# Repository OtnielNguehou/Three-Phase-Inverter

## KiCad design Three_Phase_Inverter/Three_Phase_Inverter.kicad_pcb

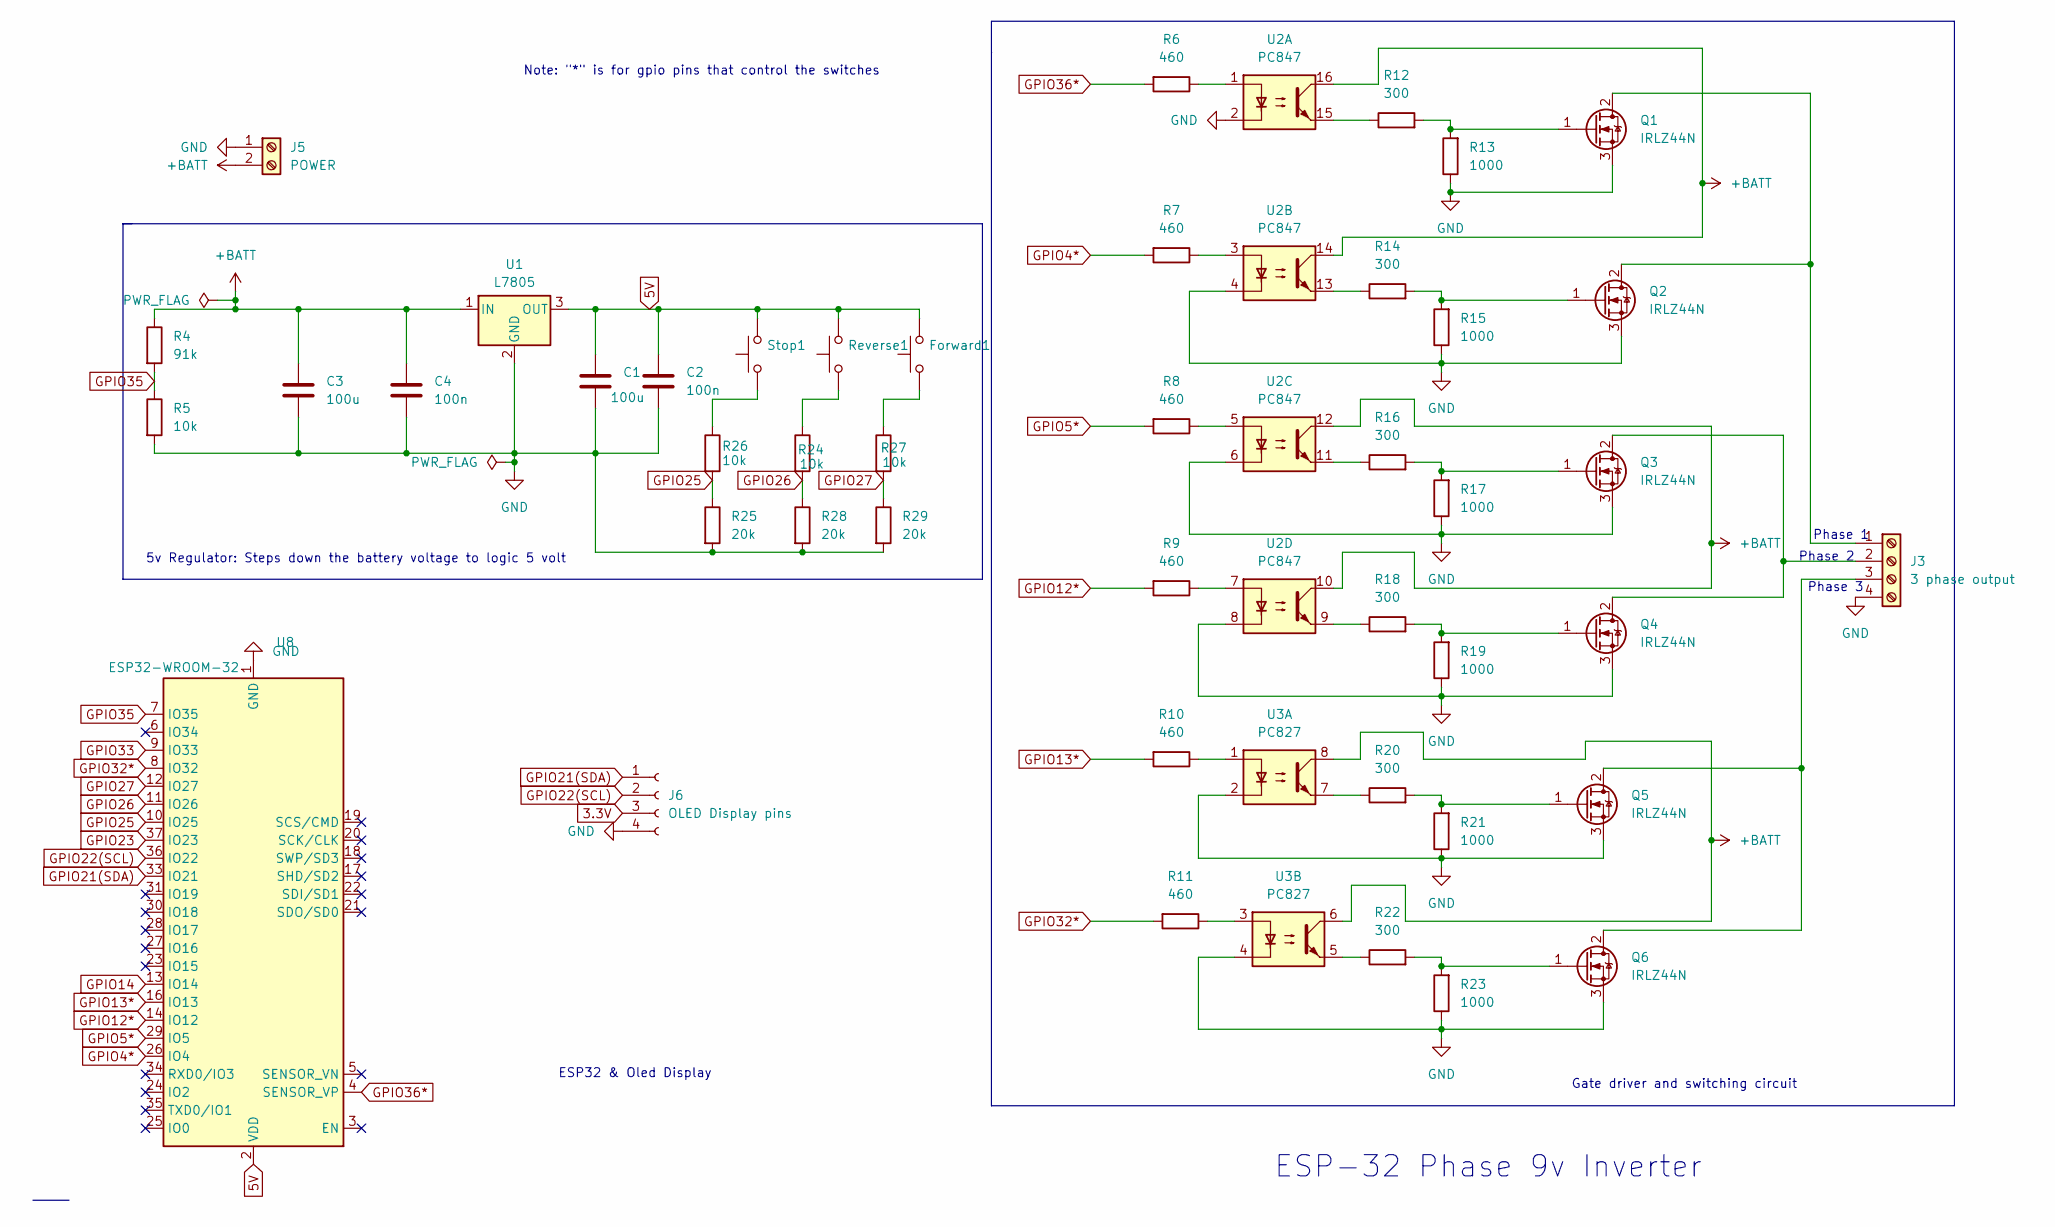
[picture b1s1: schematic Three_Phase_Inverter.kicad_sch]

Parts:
C1, C3: 100u; C_Radial_D5.0mm_H7.0mm_P2.00mm
C2, C4: 100n; C_Radial_D5.0mm_H7.0mm_P2.00mm
Forward1: SW_PUSH_6mm_H7.3mm
J3: 3 phase output; TerminalBlock_Xinya_XY308-2.54-4P_1x04_P2.54mm_Horizontal
J5: POWER; TerminalBlock_MaiXu_MX126-5.0-02P_1x02_P5.00mm
J6: OLED Display pins; PinHeader_1x04_P1.27mm_Vertical
Q1, Q2, Q3, Q4, Q5, Q6: IRLZ44N; TO-220-3_Vertical
R4: 91k; R_Axial_DIN0207_L6.3mm_D2.5mm_P10.16mm_Horizontal
R5, R24, R26, R27: 10k; R_Axial_DIN0207_L6.3mm_D2.5mm_P10.16mm_Horizontal
R6, R7, R8, R9, R10, R11: 460; R_Axial_DIN0207_L6.3mm_D2.5mm_P10.16mm_Horizontal
R12, R14, R16, R18, R20, R22: 300; R_Axial_DIN0207_L6.3mm_D2.5mm_P10.16mm_Horizontal
R13, R15, R17, R19, R21, R23: 1000; R_Axial_DIN0207_L6.3mm_D2.5mm_P10.16mm_Horizontal
R25, R28, R29: 20k; R_Axial_DIN0207_L6.3mm_D2.5mm_P10.16mm_Horizontal
Reverse1: SW_PUSH_6mm_H7.3mm
Stop1: SW_PUSH_6mm_H7.3mm
U1: L7805; TO-220-3_Vertical
U2: PC847; DIP-16_W7.62mm
U3: PC827; DIP-8_W7.62mm
U8: ESP32-WROOM-32; ESP32-C3-DevKitM-1

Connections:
3.3V: J6.3
5V: C1.1, C2.1, Forward1.2, Reverse1.2, Stop1.2, U1.3 (OUT), U8.2 (VDD)
+BATT: C3.1, C4.1, J5.2, R4.1, U1.1 (IN), U2.10, U2.12, U2.14, U2.16, U3.6, U3.8
GND: C1.2, C2.2, C3.2, C4.2, J3.4, J5.1, J6.4, Q1.3 (S), Q2.3 (S), Q3.3 (S), Q4.3 (S), Q5.3 (S), Q6.3 (S), R5.2, R13.1, R15.1, R17.1, R19.1, R21.1, R23.1, R25.2, R28.2, R29.2, U1.2 (GND), U2.2, U2.4, U2.6, U2.8, U3.2, U3.4, U8.1 (GND), U8.15 (GND), U8.38 (GND), U8.39 (GND)
GPIO4*: R7.2, U8.26 (IO4)
GPIO5*: R8.2, U8.29 (IO5)
GPIO12*: R9.2, U8.14 (IO12)
GPIO13*: R10.2, U8.16 (IO13)
GPIO14: U8.13 (IO14)
GPIO21(SDA): J6.1, U8.33 (IO21)
GPIO22(SCL): J6.2, U8.36 (IO22)
GPIO23: U8.37 (IO23)
GPIO25: R25.1, R26.2, U8.10 (IO25)
GPIO26: R24.2, R28.1, U8.11 (IO26)
GPIO27: R27.2, R29.1, U8.12 (IO27)
GPIO32*: R11.2, U8.8 (IO32)
GPIO33: U8.9 (IO33)
GPIO35: R4.2, R5.1, U8.7 (IO35)
GPIO36*: R6.2, U8.4 (SENSOR_VP)
unnamed: Forward1.1, R27.1
unnamed: J3.1, Q1.2 (D), Q2.2 (D)
unnamed: J3.2, Q3.2 (D), Q4.2 (D)
unnamed: J3.3, Q5.2 (D), Q6.2 (D)
unnamed: Q1.1 (G), R12.2, R13.2
unnamed: Q2.1 (G), R14.2, R15.2
unnamed: Q3.1 (G), R16.2, R17.2
unnamed: Q4.1 (G), R18.2, R19.2
unnamed: Q5.1 (G), R20.2, R21.2
unnamed: Q6.1 (G), R22.2, R23.2
unnamed: R6.1, U2.1
unnamed: R7.1, U2.3
unnamed: R8.1, U2.5
unnamed: R9.1, U2.7
unnamed: R10.1, U3.1
unnamed: R11.1, U3.3
unnamed: R12.1, U2.15
unnamed: R14.1, U2.13
unnamed: R16.1, U2.11
unnamed: R18.1, U2.9
unnamed: R20.1, U3.7
unnamed: R22.1, U3.5
unnamed: R24.1, Reverse1.1
unnamed: R26.1, Stop1.1

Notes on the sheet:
Gate driver and switching circuit
ESP-32 Phase 9v Inverter
Note: "*" is for gpio pins that control the switches
ESP32 & Oled Display
Phase 1
Phase 2
Phase 3
5v Regulator: Steps down the battery voltage to logic 5 volt

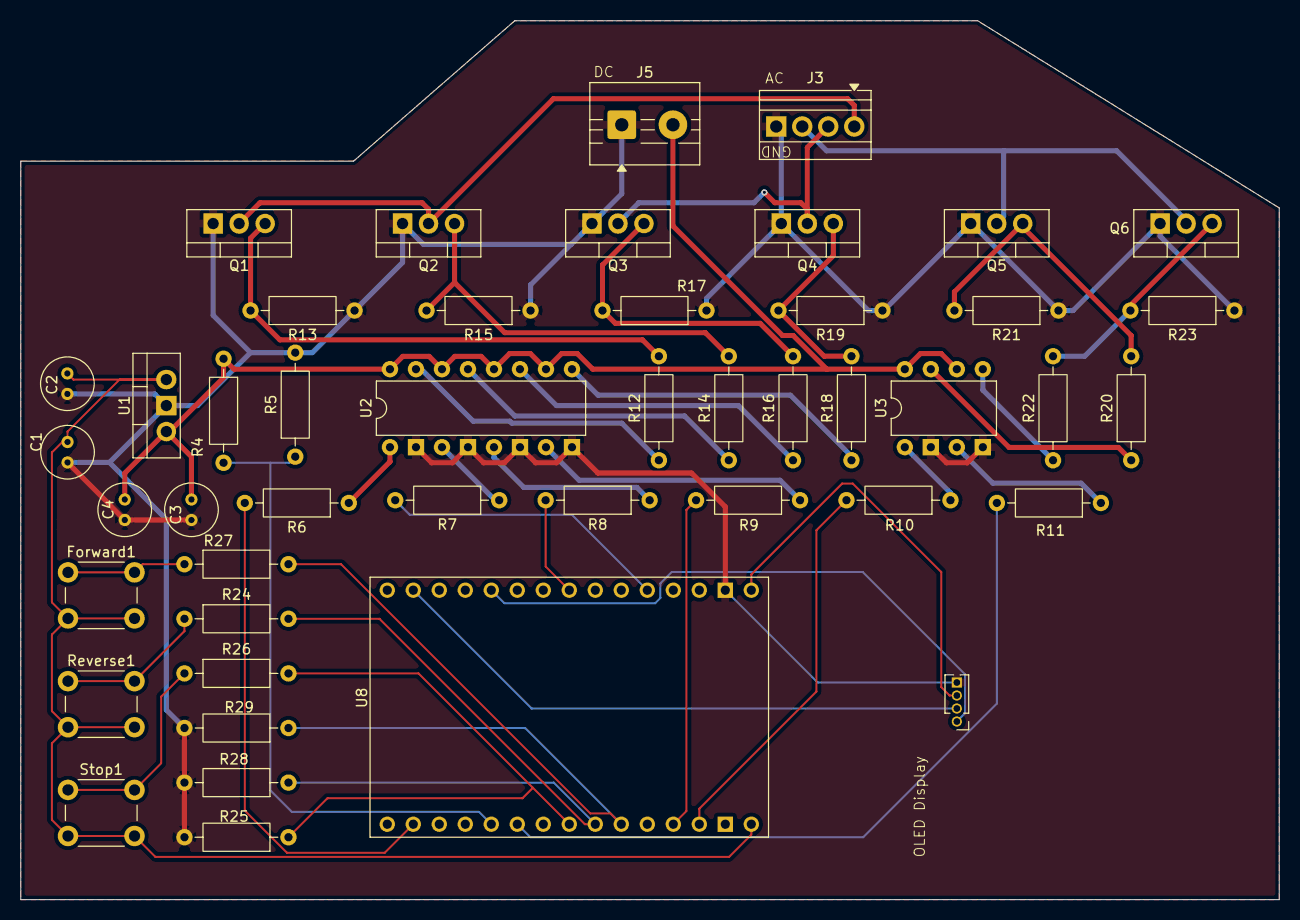
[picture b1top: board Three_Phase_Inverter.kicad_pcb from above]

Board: 2 copper layers, 122.9 x 85.9 mm, 46 parts (0 on the bottom side), 39 nets.
